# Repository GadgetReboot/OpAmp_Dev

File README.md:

# OpAmp_Dev
Breakout board for a dual Op Amp

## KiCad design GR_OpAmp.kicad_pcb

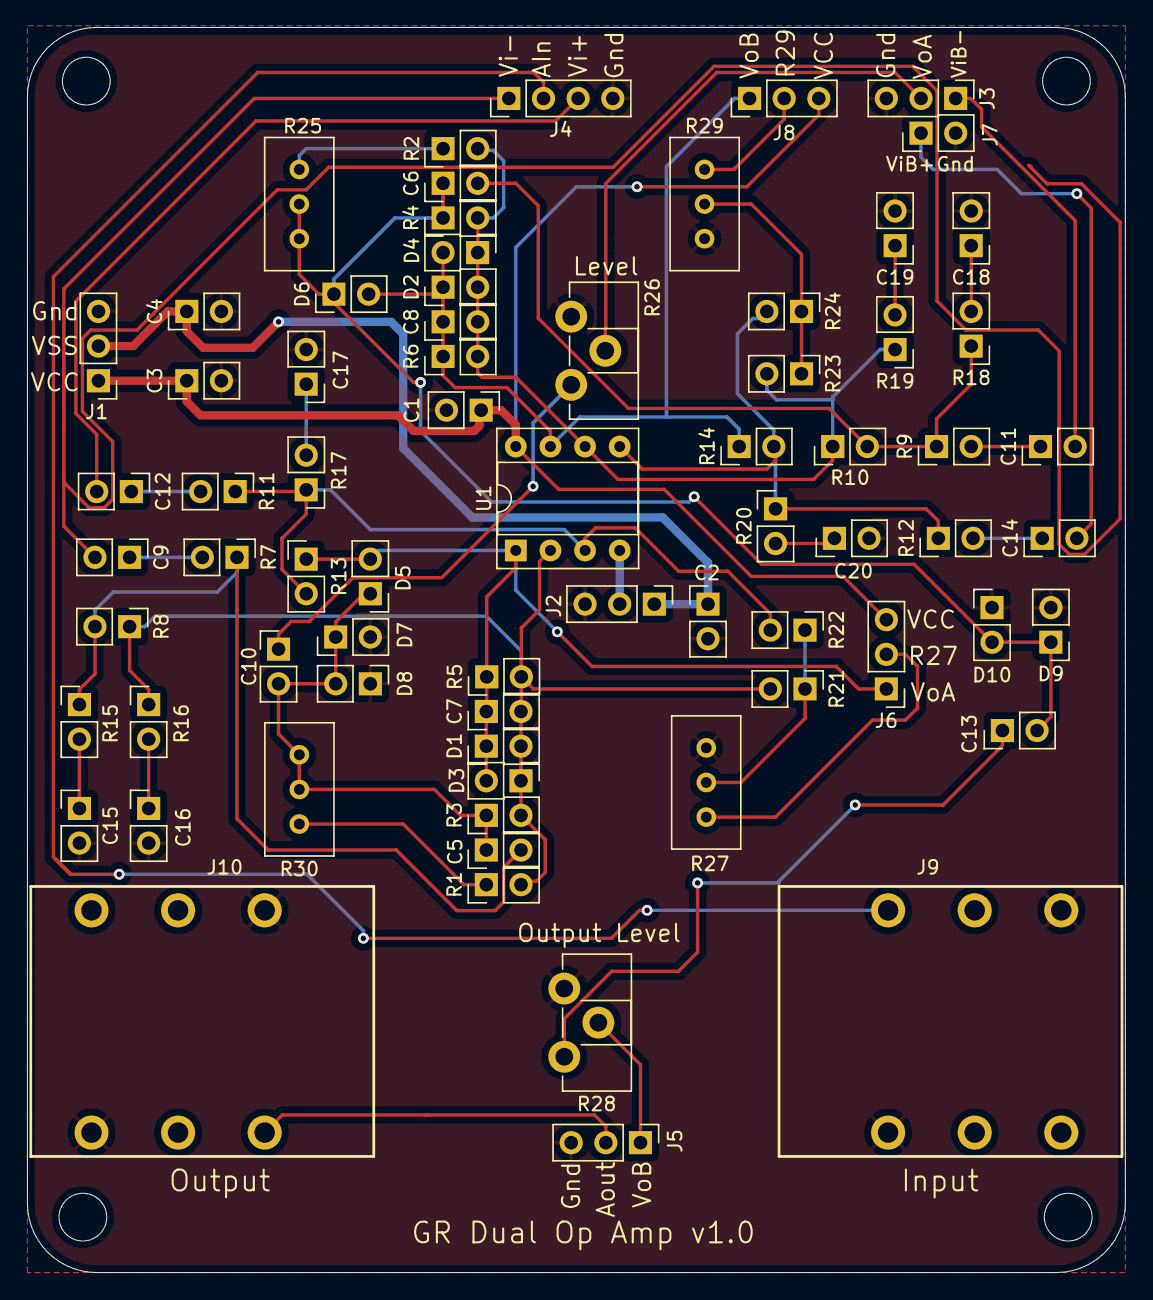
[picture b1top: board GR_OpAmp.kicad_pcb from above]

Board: 2 copper layers, 80.5 x 91.3 mm, 71 parts (0 on the bottom side), 40 nets.

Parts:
C1, C2, C3, C4, C5, C6, C7, C8, C9, C10, C11, C12, C13, C14, C15, C16, C17, C18, C19, C20: C_Small; PinHeader_1x02_P2.54mm_Vertical
D1, D2, D3, D4, D5, D6, D7, D8, D9, D10: D_Small_ALT; PinHeader_1x02_P2.54mm_Vertical
J1, J2, J3, J5, J6, J8: Conn_01x03; PinHeader_1x03_P2.54mm_Vertical
J4: Conn_01x04; PinHeader_1x04_P2.54mm_Vertical
J7: Conn_01x02; PinHeader_1x02_P2.54mm_Vertical
J9, J10: RA49B14B; Headphone_Jack_6.35mm
R1, R2, R3, R4, R5, R6, R7, R8, R9, R10, R11, R12, R13, R14, R15, R16, R17, R18, R19, R20, R21, R22, R23, R24: R_Small_US; PinHeader_1x02_P2.54mm_Vertical
R25, R27, R29, R30: R_POT_US; Potentiometer_Bourns_3296W_Vertical
R26, R28: R_POT_US; Potentiometer_ACP_CA9-H2,5_Horizontal
U1: TL072; DIP-8_W7.62mm_Socket

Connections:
/In1a+: R11.1, R13.2, R17.1, R22.2, U1.3
/In1a-: C7.2, D1.2, D3.1, R1.2, R3.2, R5.2, R8.1, R16.1, R21.2, U1.2
/In1b+: R12.1, R14.2, R20.1, R24.2, U1.5
/In1b-: C8.2, D2.2, D4.1, R2.2, R4.2, R6.2, R10.1, R19.1, R23.2, U1.6
/Out1a: C7.1, D1.1, D3.2, D5.2, J6.1, R5.1, R13.1, U1.1
/Out1b: C8.1, D2.1, D4.2, D6.2, J8.1, R6.1, R14.1, U1.7
GNDREF: C1.2, C2.2, C3.2, C4.2, C15.2, C16.2, C17.2, C18.2, C19.2, C20.2, D7.2, D8.1, D9.2, D10.1, J1.3, J2.3, J3.3, J4.4, J5.3, J7.2, J9.S, J9.TB, J10.S, J10.TB, R26.1, R27.3, R28.1, R29.3
unnamed: C5.2, R7.1, R8.2, R15.1
unnamed: C6.2, R9.1, R10.2, R18.1
unnamed: C9.1, R7.2
unnamed: C9.2, J4.1
unnamed: C10.1, R26.3
unnamed: C5.1, C10.2, D5.1, D7.1, D8.2, R3.1, R30.1, R30.2
unnamed: C11.1, R9.2
unnamed: C11.2, J3.1
unnamed: C12.1, R11.2
unnamed: C12.2, J4.3
unnamed: C13.1, R28.3
unnamed: C6.1, C13.2, D6.1, D9.1, D10.2, R4.1, R25.1, R25.2
unnamed: C14.1, R12.2
unnamed: C14.2, J7.1
unnamed: C15.1, R15.2
unnamed: C16.1, R16.2
unnamed: C17.1, R17.2
unnamed: C18.1, R18.2
unnamed: C19.1, R19.2
unnamed: C20.1, R20.2
unnamed: J2.2, U1.4
unnamed: J3.2, R26.2
unnamed: J4.2, J9.T
unnamed: J5.1, R28.2
unnamed: J6.2, R27.1
unnamed: J8.2, R29.1
unnamed: J5.2, J10.T
unnamed: R1.1, R30.3
unnamed: R2.1, R25.3
unnamed: R21.1, R22.1, R27.2
unnamed: R23.1, R24.1, R29.2
VCC: C1.1, C3.1, J1.1, J6.3, J8.3, U1.8
VSS: C2.1, C4.1, J1.2, J2.1
